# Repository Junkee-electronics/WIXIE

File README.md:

# WIXIE

a project for 2 digit nixie watch.
single button operation etc.
synchronised via RTC.
wireless charging.

//No alarms yet! (maybe in the future)
EDIT: ok, i thought about it and i think i implemented it somewhat okay.

possibly will be developing the PCB in the near future.

currently moved to a backburner, as it tested ok, but the driver chip for the nixies is KO.

if anyone is curious, ill upload the supposed k133ID1 delidded picture. by my assumption, its mighty suss.
  -of outer 16 pins, internally bonded only 14.
  -outer VCC pin isn't connected to anything, not even the base platform for the substrate (not even bonded directly to the platform, only glued).
  -lacking amount of output buffer transistors, i count only 7.
well, what could i expect from russians, huh (an attemted joke) :)

STILL DISLIKE LIBRARIES;

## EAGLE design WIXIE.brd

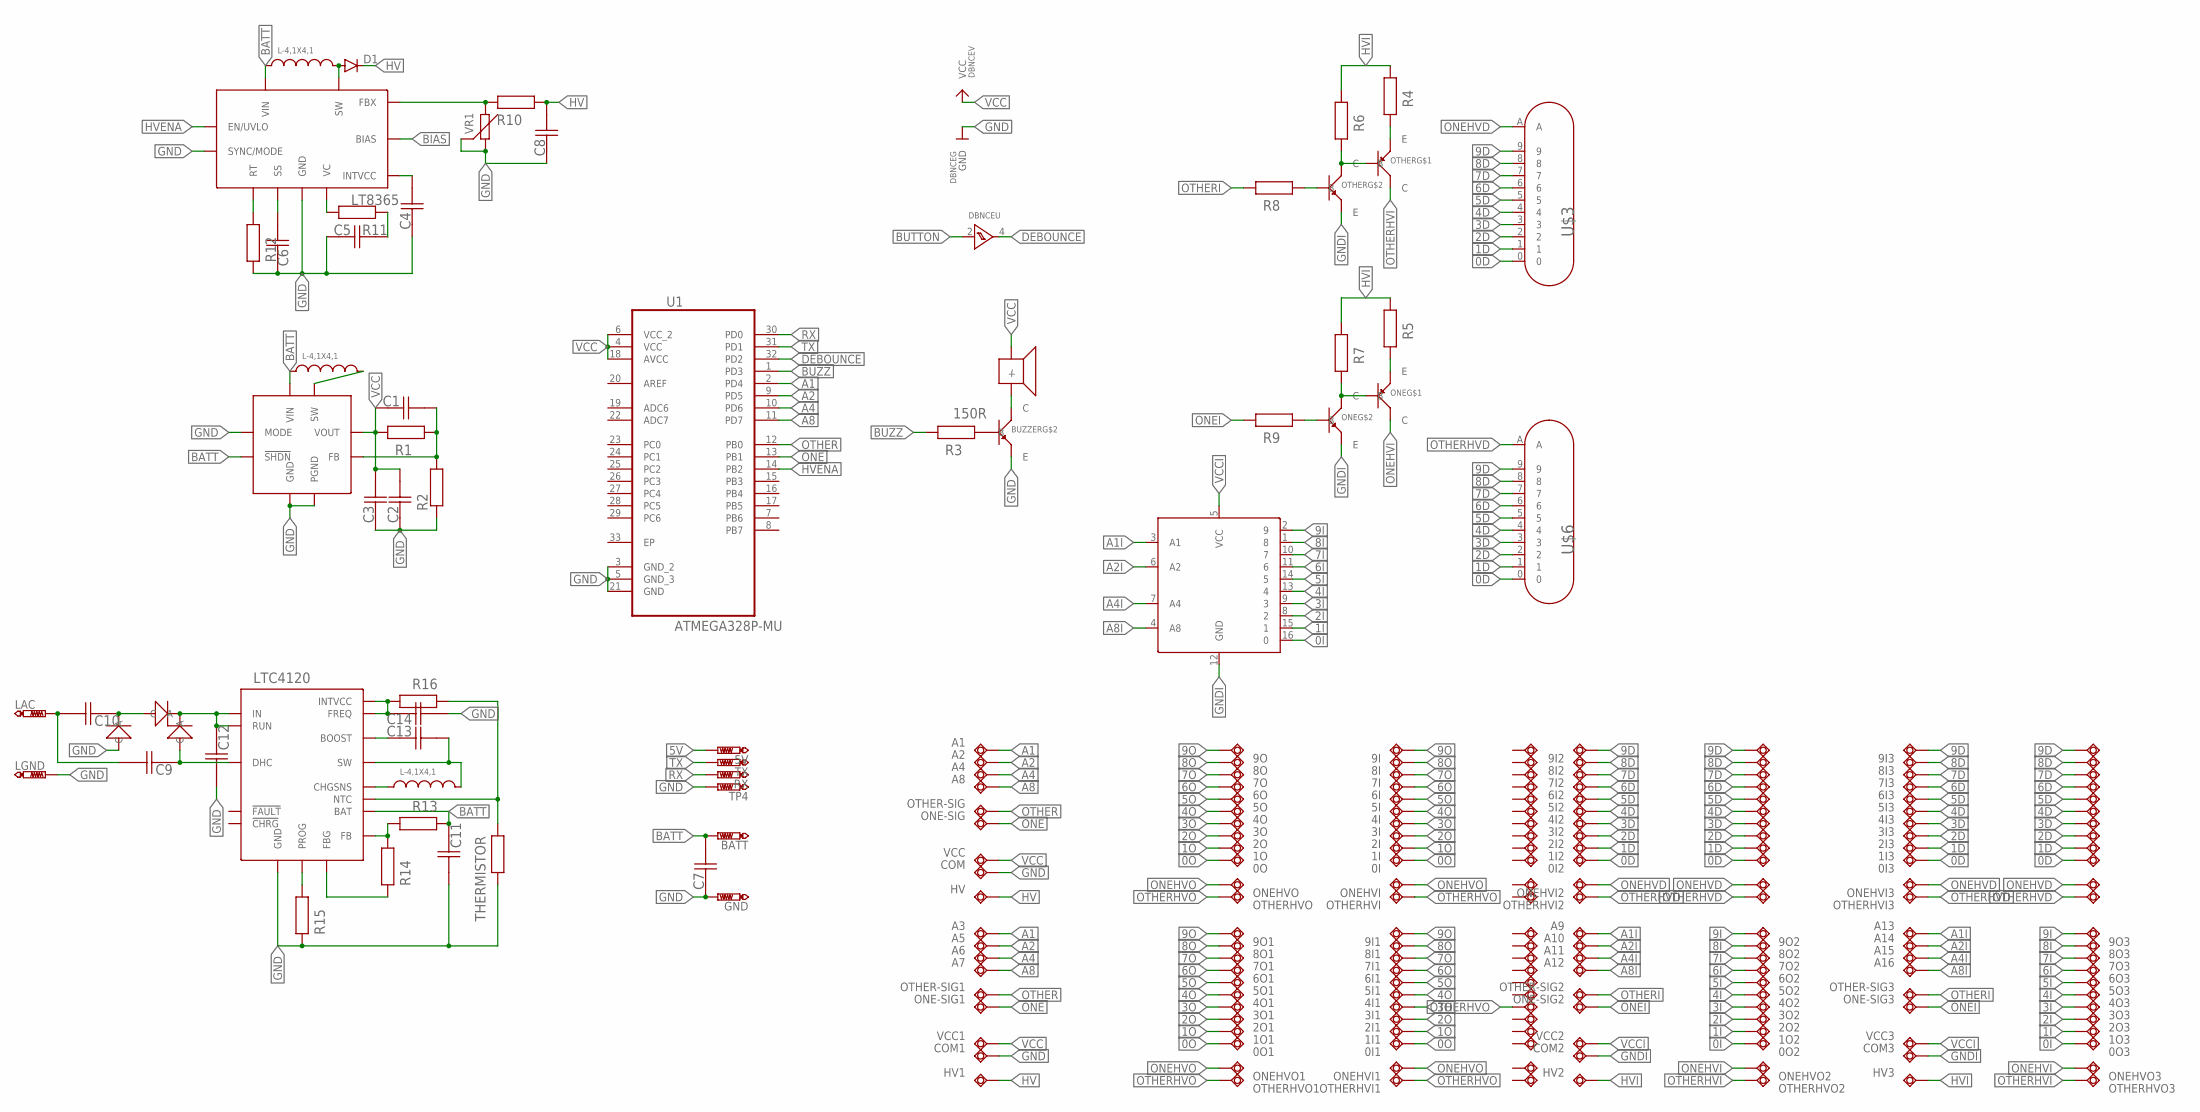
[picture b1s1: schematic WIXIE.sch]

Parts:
0I, 0I1, 0I2, 0I3, 0O, 0O1, 0O2, 0O3, 1I, 1I1, 1I2, 1I3, 1O, 1O1, 1O2, 1O3, 2I, 2I1, 2I2, 2I3, 2O, 2O1, 2O2, 2O3, 3I, 3I1, 3I2, 3I3, 3O, 3O1, 3O2, 3O3, 4I, 4I1, 4I2, 4I3, 4O, 4O1, 4O2, 4O3, 5I, 5I1, 5I2, 5I3, 5O, 5O1, 5O2, 5O3, 6I, 6I1, 6I2, 6I3, 6O, 6O1, 6O2, 6O3, 7I, 7I1, 7I2, 7I3, 7O, 7O1, 7O2, 7O3, 8I, 8I1, 8I2, 8I3, 8O, 8O1, 8O2, 8O3, 9I, 9I1, 9I2, 9I3, 9O, 9O1, 9O2, 9O3: TPSQTP12SQ; TP12SQ
5V: PTR1B1,27; B1,27
A1, A2, A3, A4, A5, A6, A7, A8, A9, A10, A11, A12, A13, A14, A15, A16: TPSQTP12SQ; TP12SQ
BATT: PTR1PAD1-13; P1-13
BUZZER: MMDT5451; SOT-363
C1, C2, C3, C4, C5, C6, C7, C8, C9, C10, C11, C12, C13, C14: CAPACITOR-0603; 0603
COM, COM1, COM2, COM3: TPSQTP12SQ; TP12SQ
D1: DIODE-SOD123; SOD123
DBNCE: 74AHC1G17; SOT-353-1
GND: PTR1PAD1-13; P1-13
HV, HV1, HV2, HV3: TPSQTP12SQ; TP12SQ
LAC: PTR1PAD1-13; P1-13
LGND: PTR1PAD1-13; P1-13
LT8365: LT8365; MSE16
LTC3539: LTC3539; DFN8-2X3
LTC4120: LTC4120; QFN16
ONE: MMDT5451; SOT-363
ONE-SIG, ONE-SIG1, ONE-SIG2, ONE-SIG3: TPSQTP12SQ; TP12SQ
ONEHVI, ONEHVI1, ONEHVI2, ONEHVI3: TPSQTP12SQ; TP12SQ
ONEHVO, ONEHVO1, ONEHVO2, ONEHVO3: TPSQTP12SQ; TP12SQ
OTHER: MMDT5451; SOT-363
OTHER-SIG, OTHER-SIG1, OTHER-SIG2, OTHER-SIG3: TPSQTP12SQ; TP12SQ
OTHERHVI, OTHERHVI1, OTHERHVI2, OTHERHVI3: TPSQTP12SQ; TP12SQ
OTHERHVO, OTHERHVO1, OTHERHVO2, OTHERHVO3: TPSQTP12SQ; TP12SQ
R1, R2, R4, R5, R6, R7, R8, R9, R10, R11, R12, R13, R14, R15, R16: RESISTOR-0603; 0603
R3: 150R; 0603
RX: PTR1B1,27; B1,27
THERMISTOR: RESISTOR-0603; 0603
TP1, TP2, TP3, TP5, TP6, TP7, TP8, TP9, TP10, TP11, TP12, TP13, TP14, TP15, TP16, TP17, TP18, TP19, TP20, TP21, TP22, TP23, TP24, TP25, TP26, TP27, TP28, TP29, TP30, TP31, TP32, TP33, TP34, TP35, TP36, TP37, TP38, TP39, TP40, TP41, TP42, TP43, TP44, TP45, TP46, TP47, TP48, TP49: TPSQTP12SQ; TP12SQ
TP4: PTR1B1,27; B1,27
TX: PTR1B1,27; B1,27
U1: ATMEGA328P-MU; QFN50P500X500X100-33N
U$2: BUZZ-8.5X8.5
U$3, U$6: IN-17
U$5, U$11, U$12: ZENER0603; 0603DIODE
U$7, U$8, U$10: L-4,1X4,1; L-4.1X4.1
U$9: K133ID1
VCC, VCC1, VCC2, VCC3: TPSQTP12SQ; TP12SQ
VR1: SR3305

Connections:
0D: 0I2.TP, 0I3.TP, TP23.TP, TP47.TP, U$3.0, U$6.0
0I: 0O2.TP, 0O3.TP, U$9.16 (0)
0O: 0I.TP, 0I1.TP, 0O.TP, 0O1.TP
1D: 1I2.TP, 1I3.TP, TP22.TP, TP34.TP, U$3.1, U$6.1
1I: 1O2.TP, 1O3.TP, U$9.15 (1)
1O: 1I.TP, 1I1.TP, 1O.TP, 1O1.TP
2D: 2I2.TP, 2I3.TP, TP21.TP, TP33.TP, U$3.2, U$6.2
2I: 2O2.TP, 2O3.TP, U$9.8 (2)
2O: 2I.TP, 2I1.TP, 2O.TP, 2O1.TP
3D: 3I2.TP, 3I3.TP, TP20.TP, TP32.TP, U$3.3, U$6.3
3I: 3O2.TP, 3O3.TP, U$9.9 (3)
3O: 3I.TP, 3I1.TP, 3O.TP, 3O1.TP
4D: 4I2.TP, 4I3.TP, TP19.TP, TP31.TP, U$3.4, U$6.4
4I: 4O2.TP, 4O3.TP, U$9.13 (4)
4O: 4I.TP, 4I1.TP, 4O.TP, 4O1.TP
5D: 5I2.TP, 5I3.TP, TP18.TP, TP30.TP, U$3.5, U$6.5
5I: 5O2.TP, 5O3.TP, U$9.14 (5)
5O: 5I.TP, 5I1.TP, 5O.TP, 5O1.TP
5V: 5V.TP
6D: 6I2.TP, 6I3.TP, TP17.TP, TP29.TP, U$3.6, U$6.6
6I: 6O2.TP, 6O3.TP, U$9.11 (6)
6O: 6I.TP, 6I1.TP, 6O.TP, 6O1.TP
7D: 7I2.TP, 7I3.TP, TP16.TP, TP28.TP, U$3.7, U$6.7
7I: 7O2.TP, 7O3.TP, U$9.10 (7)
7O: 7I.TP, 7I1.TP, 7O.TP, 7O1.TP
8D: 8I2.TP, 8I3.TP, TP15.TP, TP27.TP, U$3.8, U$6.8
8I: 8O2.TP, 8O3.TP, U$9.1 (8)
8O: 8I.TP, 8I1.TP, 8O.TP, 8O1.TP
9D: 9I2.TP, 9I3.TP, TP14.TP, TP26.TP, U$3.9, U$6.9
9I: 9O2.TP, 9O3.TP, U$9.2 (9)
9O: 9I.TP, 9I1.TP, 9O.TP, 9O1.TP
A1: A1.TP, A3.TP, U1.2 (PD4)
A1I: A9.TP, A13.TP, U$9.3 (A1)
A2: A2.TP, A5.TP, U1.9 (PD5)
A2I: A10.TP, A14.TP, U$9.6 (A2)
A4: A4.TP, A6.TP, U1.10 (PD6)
A4I: A11.TP, A15.TP, U$9.7 (A4)
A8: A7.TP, A8.TP, U1.11 (PD7)
A8I: A12.TP, A16.TP, U$9.4 (A8)
BATT: BATT.TP, C7.2, C11.1, LT8365.3 (VIN), LTC3539.4 (VIN), LTC3539.5 (!SHDN), LTC4120.09 (BAT), R13.1, U$8.P$1, U$10.P$1
BIAS: LT8365.7 (BIAS)
BUTTON: DBNCE.2 (A)
BUZZ: R3.1, U1.1 (PD3)
DEBOUNCE: DBNCE.4 (Y), U1.32 (PD2)
GND: BUZZER.1 (E), C2.1, C3.1, C4.1, C5.1, C6.1, C7.1, C8.1, C11.2, C12.2, C14.2, COM.TP, COM1.TP, DBNCE.3 (GND), GND.TP, LGND.TP, LT8365.12 (SYNC/MODE), LT8365.PAD (GND), LTC3539.2 (PGND), LTC3539.3 (GND), LTC3539.7 (MODE), LTC3539.PAD (GND), LTC4120.05 (GND), R2.1, R12.1, R15.1, THERMISTOR.2, TP4.TP, U1.3 (GND_2), U1.5 (GND_3), U1.21 (GND), U$12.POS (A), VR1.2, VR1.3
GNDI: COM2.TP, COM3.TP, ONE.1 (E), OTHER.1 (E), U$9.12 (GND)
HV: C8.2, D1.C, HV.TP, HV1.TP, R10.2
HVENA: LT8365.1 (EN/UVLO), U1.14 (PB2)
HVI: HV2.TP, HV3.TP, R4.2, R5.2, R6.2, R7.2
N22: C1.2, LTC3539.6 (FB), R1.2, R2.2
unnamed: BUZZER.6 (C), U$2.-
unnamed: LTC3539.1 (SW), U$10.P$2
unnamed: OTHER.4 (E), R4.1
unnamed: BUZZER.2 (B), R3.2
unnamed: C4.2, LT8365.5 (INTVCC)
unnamed: OTHER.5 (B), OTHER.6 (C), R6.1
unnamed: C5.2, R11.2
unnamed: OTHER.2 (B), R8.2
unnamed: D1.A, LT8365.14 (SW), LT8365.16 (SW), U$8.P$2
unnamed: LT8365.9 (FBX), R10.1, VR1.1
unnamed: C10.1, U$5.POS (A), U$12.NEG (C)
unnamed: C9.2, C10.2, LAC.TP
unnamed: LT8365.8 (VC), R11.1
unnamed: C6.2, LT8365.11 (SS)
unnamed: LT8365.10 (RT), R12.2
unnamed: C12.1, LTC4120.03 (IN), LTC4120.16 (RUN), U$5.NEG (C), U$11.NEG (C)
unnamed: C9.1, LTC4120.06 (DHC), U$11.POS (A)
unnamed: LTC4120.13 (PROG), R15.2
unnamed: LTC4120.11 (FBG), R14.1
unnamed: LTC4120.10 (FB), R13.2, R14.2
unnamed: LTC4120.12 (NTC), R16.1, THERMISTOR.1
unnamed: LTC4120.08 (CHGSNS), U$7.P$1
unnamed: C13.2, LTC4120.04 (SW), U$7.P$2
unnamed: C13.1, LTC4120.02 (BOOST)
unnamed: C14.1, LTC4120.01 (INTVCC), LTC4120.07 (FREQ), R16.2
unnamed: ONE.2 (B), R9.2
unnamed: ONE.4 (E), R5.1
unnamed: ONE.5 (B), ONE.6 (C), R7.1
ONE: ONE-SIG.TP, ONE-SIG1.TP, U1.13 (PB1)
ONEHVD: ONEHVI2.TP, ONEHVI3.TP, TP24.TP, TP48.TP, U$3.A
ONEHVI: ONE.3 (C), ONEHVO2.TP, ONEHVO3.TP
ONEHVO: ONEHVI.TP, ONEHVI1.TP, ONEHVO.TP, ONEHVO1.TP
ONEI: ONE-SIG2.TP, ONE-SIG3.TP, R9.1
OTHER: OTHER-SIG.TP, OTHER-SIG1.TP, U1.12 (PB0)
OTHERHVD: OTHERHVI2.TP, OTHERHVI3.TP, TP25.TP, TP49.TP, U$6.A
OTHERHVI: OTHER.3 (C), OTHERHVO2.TP, OTHERHVO3.TP
OTHERHVO: OTHERHVI.TP, OTHERHVI1.TP, OTHERHVO.TP, OTHERHVO1.TP, TP8.TP
OTHERI: OTHER-SIG2.TP, OTHER-SIG3.TP, R8.1
RX: RX.TP, U1.30 (PD0)
TX: TX.TP, U1.31 (PD1)
VCC: C1.1, C2.2, C3.2, DBNCE.5 (VCC), LTC3539.8 (VOUT), R1.1, U1.4 (VCC), U1.6 (VCC_2), U1.18 (AVCC), U$2.+, VCC.TP, VCC1.TP
VCCI: U$9.5 (VCC), VCC2.TP, VCC3.TP

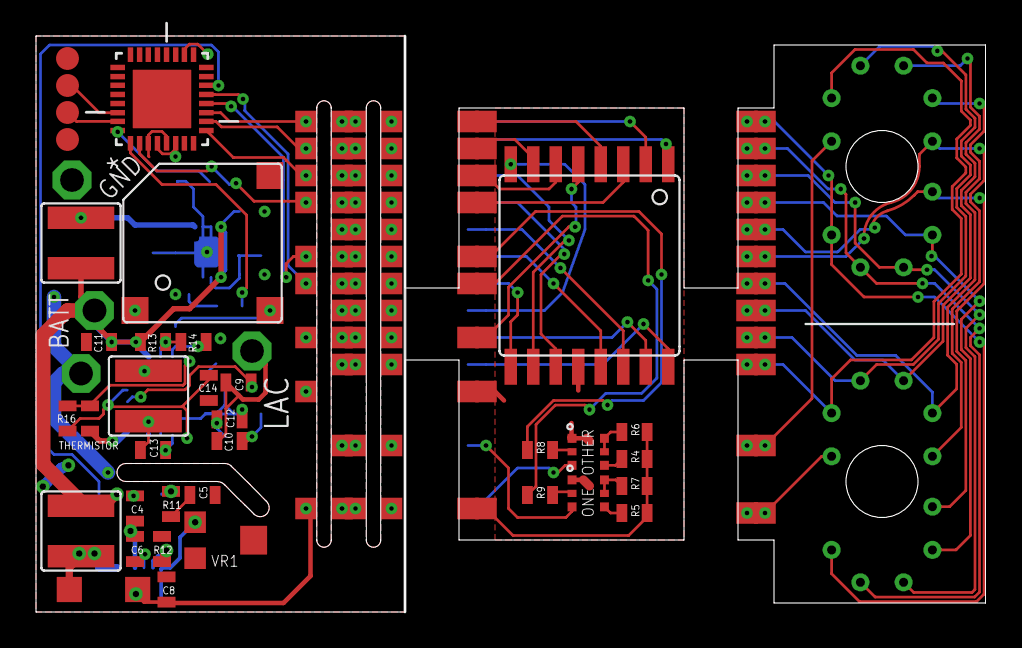
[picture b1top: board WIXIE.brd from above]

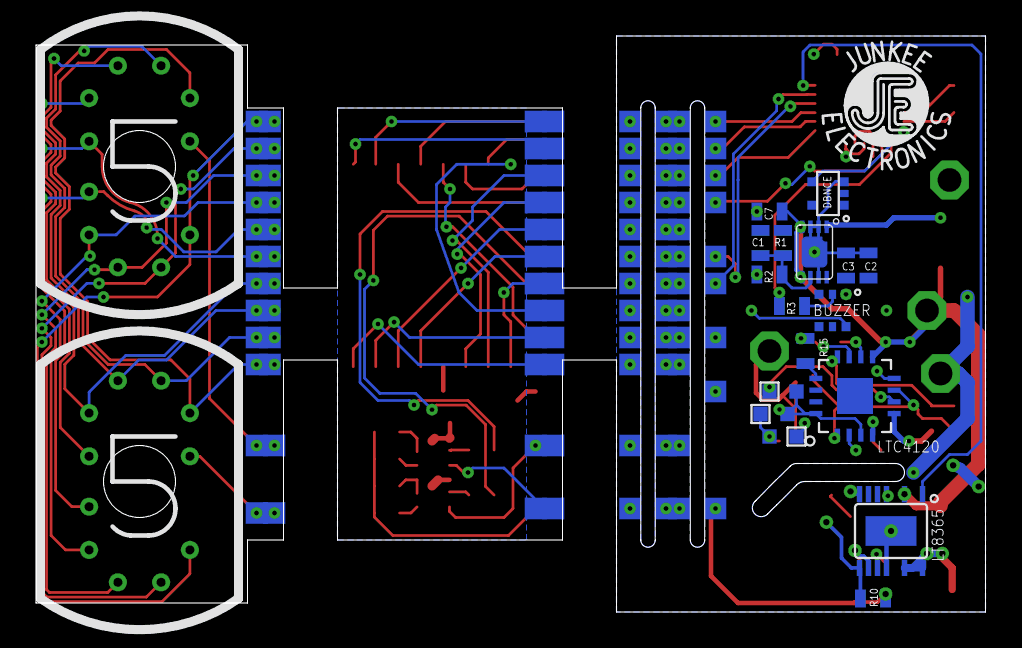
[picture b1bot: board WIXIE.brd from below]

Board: 2 copper layers, 52.8 x 32.0 mm, 240 parts (113 on the bottom side), 89 nets.

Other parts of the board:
U$1: LOGO

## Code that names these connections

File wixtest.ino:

//#include "RTClib.h"

#define bttn 2
#define A 4
#define B 5
#define C 6
#define D 7
#define one 8
#define other 9
#define battpin A0

//RTC_DS1307 rtc;

uint8_t sec;
uint8_t minor;
uint8_t major;
uint8_t batt;
uint8_t desired;

int unsigned battstate;

long unsigned trigger;
long unsigned RFRSH = 0;
long unsigned holdtime = 0;

bool ena = true;
bool call = true;
bool hold = false;
bool lhold = false;
bool oneother = true;
bool set = false;

//______________________________________________________________________

void state() {
    RFRSH = millis();
    holdtime = millis();
    call = true;
    set = true;
}

//______________________________________________________________________

void setup() {

Serial.begin(9600);
  
  pinMode(A, OUTPUT);
  pinMode(B, OUTPUT);
  pinMode(C, OUTPUT);
  pinMode(D, OUTPUT);
  pinMode(one, OUTPUT);
  pinMode(other, OUTPUT);
  pinMode(bttn, INPUT_PULLUP);

//  rtc.begin();
//stop interrupts
  cli();

  attachInterrupt(digitalPinToInterrupt(bttn), state, FALLING);

//set timer0 interrupt at 500Hz
  TCCR0A = 0;// set entire TCCR0A register to 0
  TCCR0B = 0;// same for TCCR0B
  TCNT0  = 0;//initialize counter value to 0
  // set compare match register for 500hz increments
  OCR0A = 124;// = (16*10^6) / (500*64) - 1 (must be <256)
  // turn on CTC mode
  TCCR0A |= (1 << WGM01);
  // Set CS02 bit for 256 prescaler
  TCCR0B |= (1 << CS02);   
  // enable timer compare interrupt
  TIMSK0 |= (1 << OCIE0A);

//set timer1 interrupt at 1Hz
  TCCR1A = 0;// set entire TCCR1A register to 0
  TCCR1B = 0;// same for TCCR1B
  TCNT1  = 0;//initialize counter value to 0
  // set compare match register for 1hz increments
  OCR1A = 15624;// = (16*10^6) / (1*1024) - 1 (must be <65536)
  // turn on CTC mode
  TCCR1B |= (1 << WGM12);
  // Set CS12 and CS10 bits for 1024 prescaler
  TCCR1B |= (1 << CS12) | (1 << CS10);  
  // enable timer compare interrupt
  TIMSK1 |= (1 << OCIE1A);
/*
  DateTime now = rtc.now();
  sec = now.second();
  min = now.minute();
  hr = now.hour();
  day = now.day();
  month = now.month();
  year = now.year();
  trigger = millis();
*/
  sei();//allow interrupts
}

//______________________________________________________________________
//timer1 interrupt 1Hz

ISR(TIMER1_COMPA_vect){
  sec++;
}

//______________________________________________________________________
//timer0 interrupt 500Hz

ISR(TIMER0_COMPA_vect){
  if (call){
    if (oneother){
      PORTD &= 0b00000111;
      PORTB &= 0b11000000;
      PORTB |= 0b00000001;
      PORTD = PORTD | minor;
      oneother = false;
    }
    else{
      PORTD &= 0b00000101;
      PORTB &= 0b11000000;
      PORTB |= 0b00000010;
      PORTD = PORTD | major;
      oneother = true;
    }
  }
  else {
     PORTD &= 0b00000111;
     PORTB &= 0b11000000;
  }
}

//______________________________________________________________________

void loop() {

/*
  Serial.print("sec");
  Serial.print(sec);
  Serial.print("hold");
  Serial.print(hold);
  Serial.print("lhold");
  Serial.print(lhold);
  Serial.print("oneother");
  Serial.print(oneother);
  Serial.print("batt");
  Serial.print(batt);
  Serial.print("ena");
  Serial.print(ena);
  Serial.print("call");
  Serial.print(call);
  Serial.print("minor");
  Serial.print(minor);
  Serial.print("major");
  Serial.print(major);
  Serial.print("POTRD");
  Serial.print(PORTD);
  Serial.print("POTRB");
  Serial.println(PORTB);
*/

//safety for if millis eventually overflows, the time will stay updated from the RTC in 10 hour intervals.
//  if (millis() < trigger) trigger = millis();
  
/*
  if ((millis() - trigger) > 36000000){
    DateTime now = rtc.now();
    sec = now.second();
    min = now.minute();
    hr = now.hour();
    day = now.day();
    month = now.month();
    year = (now.year())-2000;
    trigger = millis();
  }
*/

  holder();
/*  
  if (lhold){
    RFRSH = millis();
    for (uint8_t i = 0; i < 5; i++){
      while ((millis() - RFRSH)<=5000){
        switch (i){
          case 0:
            adjuster(sec);
          break;
          case 1:
            adjuster(min);
          break;
          case 2:
            adjuster(hr);
          break;
          case 3:
            adjuster(day);
          break;
          case 4:
            adjuster(month);
          break;
          case 5:
            adjuster(year);
          break;
        }
      manager();
      }
    }
//  rtc.adjust(DateTime((year + 2000), month, day, hr, min, sec));
  }
*/
  //manages the battery, and does a check of whether the battery isnt too far discharged
  battstate =  analogRead(battpin);
  batt = (int) (battstate * 5 * 100) / (4.25 * 1024);
  if (batt > 99) batt = 99;
  if (batt > 0) ena = true;
  else ena = false;

// separation of digit one and two, bitshifting them to the left. now take it back now ya'll
  if (hold){
    convert(batt);
    call = false;
  }

  manager();
/*
  if (ena){
    if ((millis() - RFRSH)<500) desired = 0;
    if (500<=(millis() - RFRSH)<1000) desired = 1;
    if (1000<=(millis() - RFRSH)<1500) desired = 2;
    if (1500<=(millis() - RFRSH)<2000) desired = 3;
    if (2000<=(millis() - RFRSH)<2500) desired = 4;
    if (2500<=(millis() - RFRSH)<3000) desired = 5;
  }
  */
  convert(sec);
//  else call = false;
}

//determines a long button press or even longer button press
void holder(){
  if ((500 <= (millis() - holdtime) <= 2000) && !digitalRead(bttn)){
    hold = true;
    lhold = false;
  }
  else if (((millis() - holdtime) > 2000) && !digitalRead(bttn)){
    hold = false;
    lhold = true;
  }
  else {
    hold = false;
    lhold = false;
  }
}

//converts double digits to single digits and splits them according to what should be displayed now
void convert(uint8_t vale){
  minor = ((vale % 10)<<4);
  major = (((int) vale / 10)<<4);
}

// do some computing for time management, like 60 sec in minute, 60 of them in hour, 24 hr. cycle etc.
void manager(){  
  if (sec >= 60){
    sec = 0;
  }
}

void adjuster(uint8_t val){
  holder();
  if (set){
    val++;
    set = false;
  }
  if (hold || lhold)RFRSH = millis() - 5000;
}
